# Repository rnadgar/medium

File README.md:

# OpenRegister — Zigbee Smart HVAC Register

A battery-powered, drop-in smart floor register for **room-by-room temperature
control** with Home Assistant. Replaces a standard 4"×10" floor register with a
3D-printed unit containing a stepper-driven damper, limit switches, a
differential-pressure fail-safe, and a Zigbee radio that runs 1–2+ years on
4× AA lithium cells.

```
Wall temp sensor ──► Home Assistant ──► Zigbee ──► register damper position
                          ▲                              │
                          └──── pressure / battery ◄─────┘
```

| PCB rev A (front) | Mechanism (faceplate hidden) |
|---|---|
|  |  |

## Highlights

- **Zigbee sleepy end device** (ESP32-C6) — pairs with Zigbee2MQTT or ZHA and
  appears in Home Assistant as a `cover` entity with a position slider.
- **Fine-grained damper control** — 28BYJ-48 geared stepper (bipolar-modified,
  DRV8833 driver) with limit switches for homing; motor fully de-energized
  between moves.
- **Autonomous pressure fail-safe** — an onboard differential pressure sensor
  trips the damper fully open if duct static pressure exceeds a threshold,
  with **no network dependency**; an HA-side blueprint additionally keeps the
  total open area across all registers above a configurable floor.
- **Ultra-low power** — ~150 µA average draw ⇒ ≈2.4 years on 4× AA lithium
  (see [docs/power-budget.md](docs/power-budget.md)).
- **Fully parametric CAD** — the whole register is generated from one
  parameters dataclass ([build123d](https://build123d.readthedocs.io/)), so
  other register sizes are a preset away.

## Repository layout

| Path | Contents |
|---|---|
| [`docs/`](docs/) | Architecture, power budget, BOM, assembly, pairing guides |
| [`firmware/`](firmware/) | ESP-IDF + esp-zigbee-sdk firmware (C) with host-runnable unit tests |
| [`hardware/pcb/`](hardware/pcb/) | KiCad schematic + layout, fab outputs |
| [`cad/`](cad/) | build123d parametric models, STL/STEP export, pytest checks |
| [`homeassistant/`](homeassistant/) | Zigbee2MQTT converter, ZHA quirk, HA blueprints |

## Getting started

1. **Read** [docs/architecture.md](docs/architecture.md) for the system design.
2. **Buy** the parts in [docs/bom.md](docs/bom.md).
3. **Print** the register: `cd cad && pip install -e . && python export.py`
   then print the STLs in `cad/out/stl/` ([docs/assembly.md](docs/assembly.md)).
4. **Flash** the firmware: `cd firmware && idf.py set-target esp32c6 && idf.py flash`.
5. **Pair** with Zigbee2MQTT and import the blueprints
   ([docs/pairing-setup.md](docs/pairing-setup.md)).

## Status

Rev A — design complete, hardware validation in progress. Firmware bring-up
happens on an ESP32-C6-DevKitC-1 with breakout boards **before** ordering the
custom PCB; see the dev-bench section of the BOM.

## License

MIT — see [LICENSE](LICENSE).

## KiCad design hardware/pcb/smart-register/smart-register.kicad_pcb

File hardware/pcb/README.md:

# smart-register rev A — PCB

58 × 38 mm 2-layer board for the e-bay of the smart register. ESP32-C6-MINI-1
(Zigbee), TPS62125 always-on 3.3 V buck, DRV8833 stepper driver on a
TPS22810-switched battery rail, SiP32431-switched 3.3 V sensor rail,
XGZP6897D on-board differential pressure sensor (or SDP810 on the J5 remote
header), gated battery divider, limit-switch inputs, USB-C flash/debug.

## Layout facts

- Outline/mounting contract with `cad/smart_register/params.py`:
  58 × 38 mm, M3 holes inset 3.5 mm from each corner.
- ESP32-C6 antenna at the **left board edge** with a copper/track keep-out
  under it; the CAD e-bay mounts the board vertically so this edge sits in
  the top 15 mm of the register (above the steel boot line).
- Net classes: `Default` 0.3 mm / 0.2 mm clearance; `USB` (fine-pitch USB-C
  and WSON buck nets) 0.2 mm / 0.13 mm.
- DRC: clean under KiCad 8 with the project file's net classes and severity
  settings (silk cosmetics and lib checks off — all footprints are embedded).

## Regenerating everything

The whole board is **generated from code** — do not hand-edit the outputs;
edit `tools/design.py` (netlist), `tools/gen_pcb.py` (placement), or the
generators, then:

```bash
cd hardware/pcb/tools
python3 design.py            # validate the canonical netlist
python3 gen_project.py       # .kicad_pro + lib tables
python3 gen_schematic.py     # smart-register.kicad_sch
python3 check_netlist.py     # schematic netlist == design.py (kicad-cli)
python3 gen_pcb.py           # placed board + Specctra DSN
java -jar freerouting.jar -de ../smart-register/smart-register.dsn \
     -do ../smart-register/smart-register.ses -mp 30
python3 import_ses.py        # tracks/vias + repairs + pours + stitching + DRC
python3 gen_fab.py           # gerbers/drill/BOM/CPL into ../fab/
```

Requires KiCad 7+ (pcbnew python + kicad-cli) and Java 17+ for
[Freerouting](https://github.com/freerouting/freerouting). The committed
`smart-register.ses` reproduces the committed routing exactly; only re-run
Freerouting if you change the design, and re-check DRC afterwards
(`import_ses.py` prints "DRC real issues: none" on success — its hand-repair
coordinates in `REPAIRS` are tied to the committed session and must be
revisited after any re-route).

## Ordering (JLCPCB)

1. Upload `fab/smart-register-gerbers.zip` — 2-layer, 1.6 mm FR4, any color,
   HASL or ENIG, no special options.
2. Optional assembly: `fab/bom.csv` + `fab/cpl.csv` (verify rotations in
   their preview — generated rotations follow KiCad, JLC sometimes differs
   per package).
3. **Order after validating firmware on the dev bench** (see
   `docs/bom.md` section E) — the board is validation, not the critical path.

## Bring-up checklist

1. Visual + shorts check (VBAT–GND, 3V3–GND).
2. Batteries in (or USB — SS14 feeds the pack rail at ~4.7 V for bench work):
   3.3 V rail present, ~40 µA sleep draw after flashing.
3. Flash via USB-C (`idf.py -p /dev/ttyACM0 flash` — USB-Serial-JTAG).
4. `MOTOR_PWR_EN` high → VMOT = pack voltage, sensor rail 3.3 V.
5. Motor moves, limit switches read, pressure sample returns plausible Pa.
6. Join Zigbee, then the `docs/pairing-setup.md` flow.

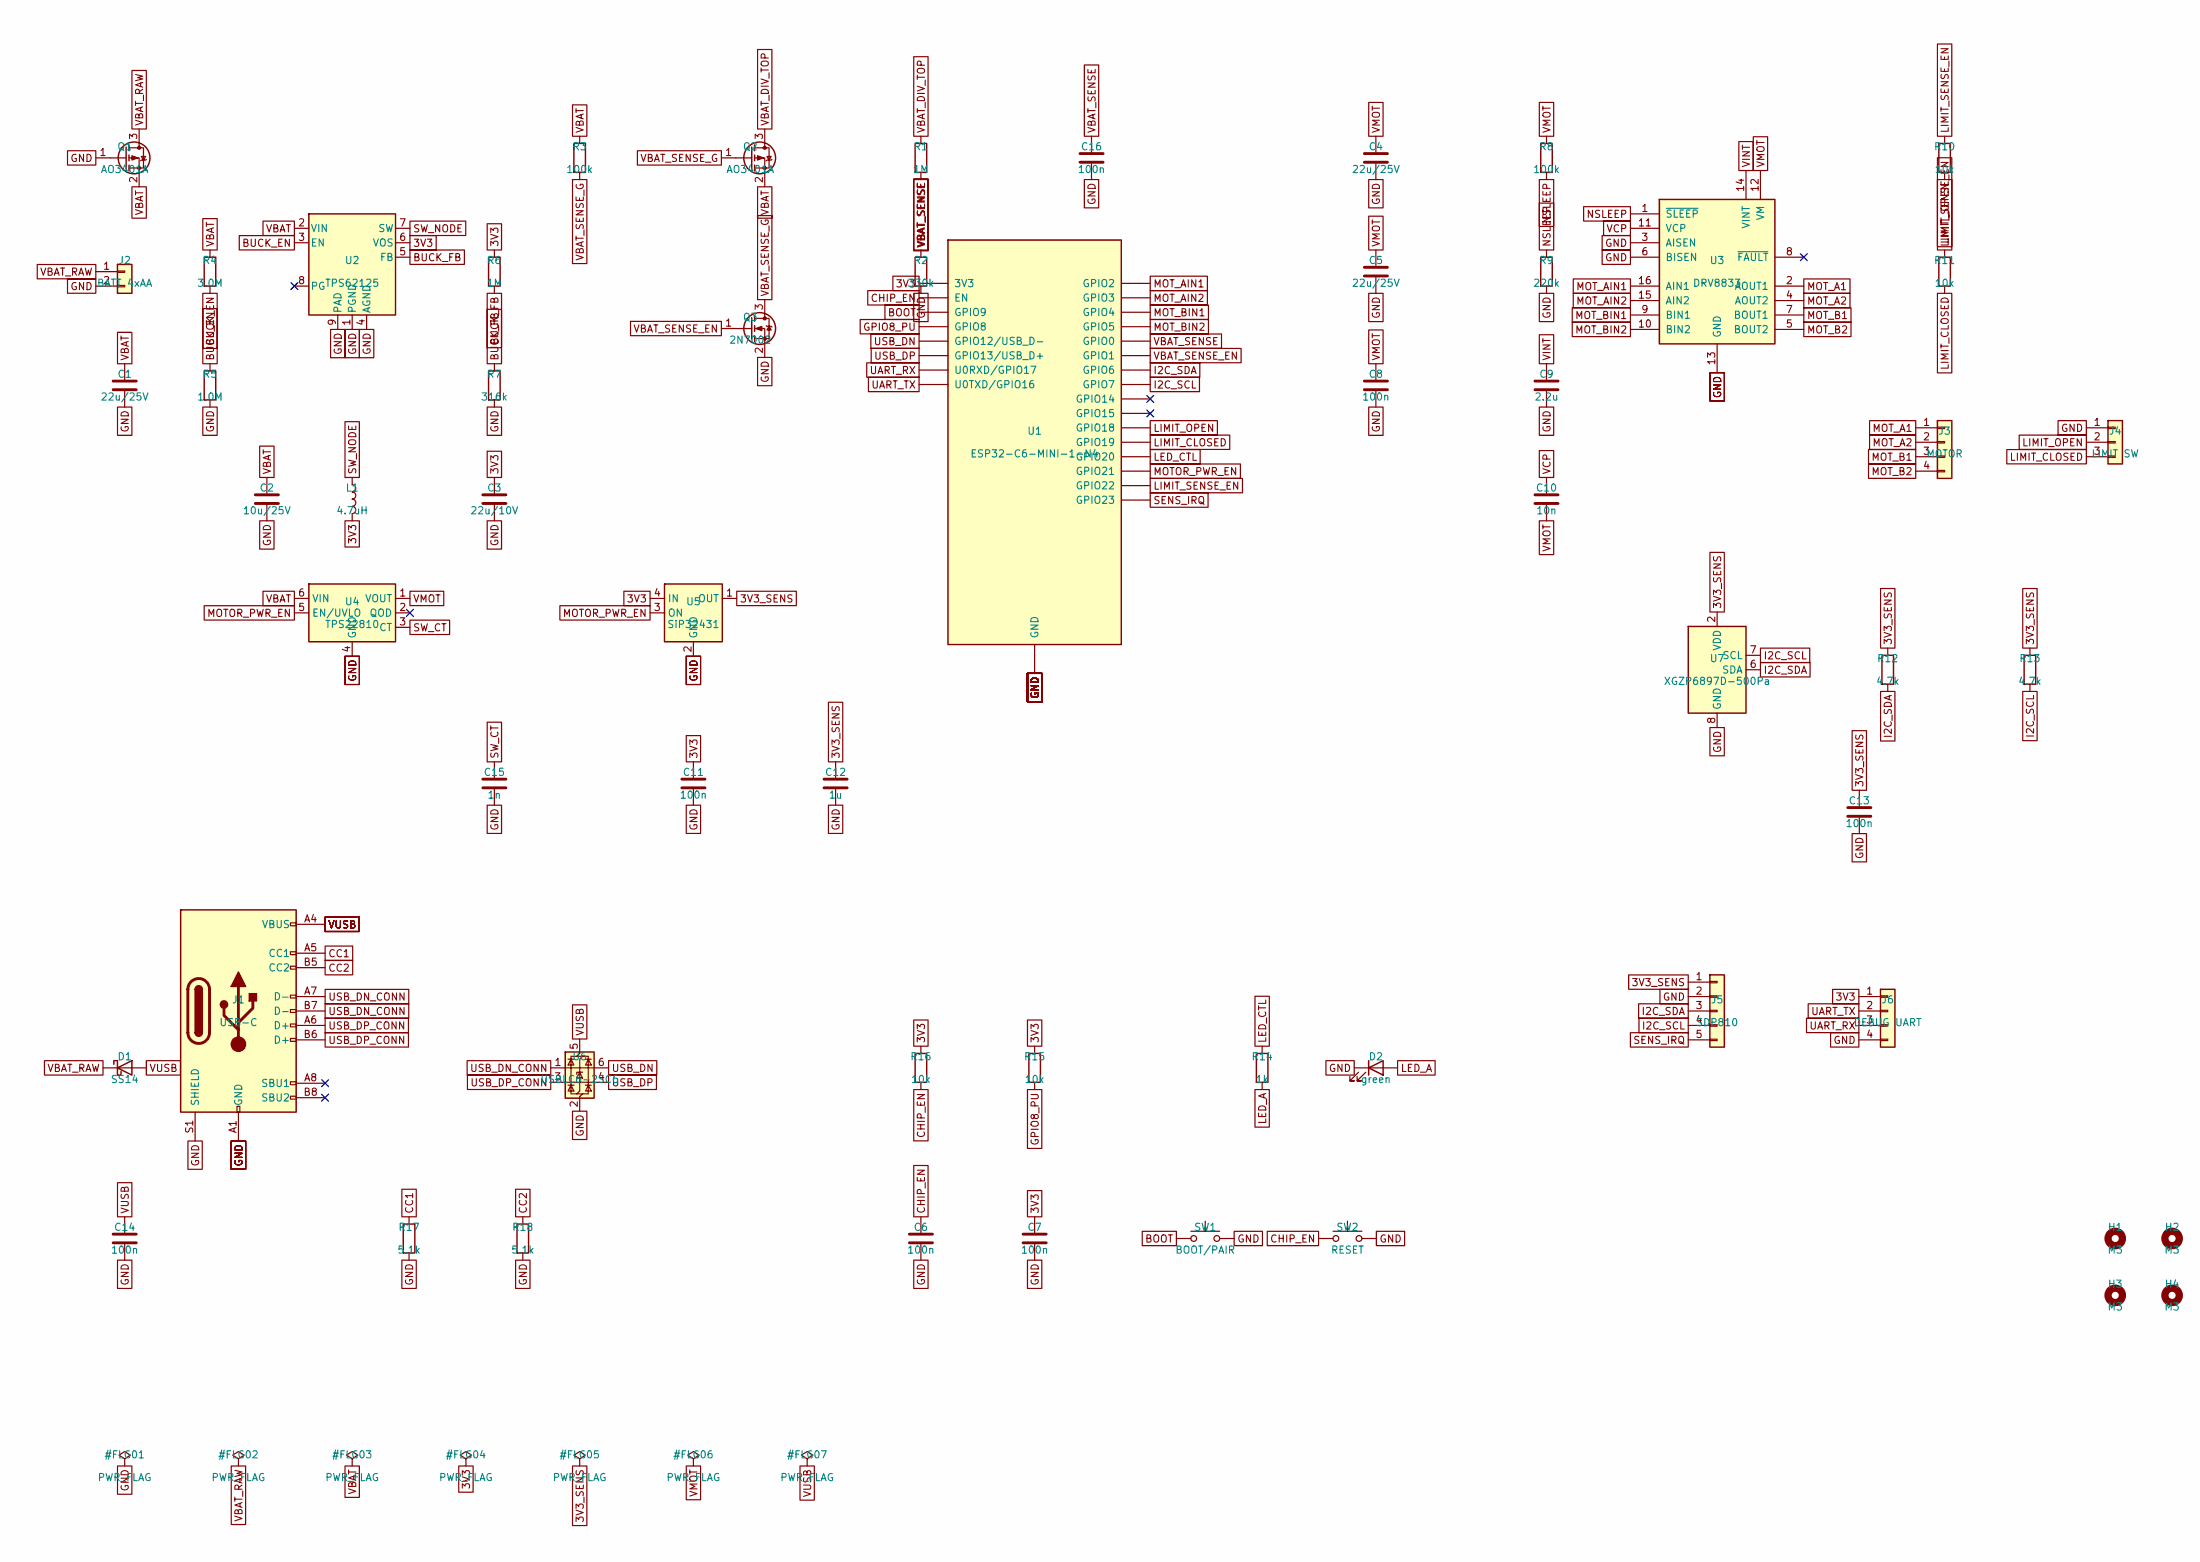
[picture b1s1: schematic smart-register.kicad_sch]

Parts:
C1, C4, C5: 22u/25V; C_1206_3216Metric; MPN GRM31CR61E226KE15
C2: 10u/25V; C_0805_2012Metric; MPN GRM21BR61E106KA73
C3: 22u/10V; C_0805_2012Metric; MPN GRM21BR61A226ME44
C6, C7, C8, C11, C13, C14, C16: 100n; C_0603_1608Metric; MPN CL10B104KB8NNNC
C9: 2.2u; C_0603_1608Metric; MPN CL10A225KP8NNNC
C10: 10n; C_0603_1608Metric; MPN CL10B103KB8NNNC
C12: 1u; C_0603_1608Metric; MPN CL10A105KB8NNNC
C15: 1n; C_0603_1608Metric; MPN CL10B102KB8NNNC
D1: SS14; D_SMA; MPN SS14
D2: green; LED_0603_1608Metric; MPN 150060GS75000
H1, H2, H3, H4: M3; MountingHole_3.2mm_M3
J1: USB-C; USB_C_Receptacle_GCT_USB4105-xx-A_16P_TopMnt_Horizontal; MPN GCT USB4105-GF-A
J2: BATT 4xAA; JST_PH_S2B-PH-K_1x02_P2.00mm_Horizontal; MPN JST S2B-PH-K-S
J3: MOTOR; JST_PH_B4B-PH-K_1x04_P2.00mm_Vertical; MPN JST B4B-PH-K-S
J4: LIMIT SW; JST_PH_B3B-PH-K_1x03_P2.00mm_Vertical; MPN JST B3B-PH-K-S
J5: SDP810; PinHeader_1x05_P2.54mm_Vertical; MPN header 1x5
J6: DEBUG UART; PinHeader_1x04_P2.54mm_Vertical; MPN header 1x4
L1: 4.7uH; L_Coilcraft_LPS4018; MPN LPS4018-472MRB
Q1, Q2: AO3401A; SOT-23; MPN AO3401A
Q3: 2N7002; SOT-23; MPN 2N7002-7-F
R1, R6: 1M; R_0603_1608Metric; MPN RC0603FR-071ML
R2: 330k; R_0603_1608Metric; MPN RC0603FR-07330KL
R3, R8: 100k; R_0603_1608Metric; MPN RC0603FR-07100KL
R4: 3.0M; R_0603_1608Metric; MPN RC0603FR-073ML
R5: 1.0M; R_0603_1608Metric; MPN RC0603FR-071ML
R7: 316k; R_0603_1608Metric; MPN RC0603FR-07316KL
R9: 220k; R_0603_1608Metric; MPN RC0603FR-07220KL
R10, R11, R15, R16: 10k; R_0603_1608Metric; MPN RC0603FR-0710KL
R12, R13: 4.7k; R_0603_1608Metric; MPN RC0603FR-074K7L
R14: 1k; R_0603_1608Metric; MPN RC0603FR-071KL
R17, R18: 5.1k; R_0603_1608Metric; MPN RC0603FR-075K1L
SW1: BOOT/PAIR; SW_Push_1P1T_NO_CK_KMR2; MPN KMR221GLFS
SW2: RESET; SW_Push_1P1T_NO_CK_KMR2; MPN KMR221GLFS
U1: ESP32-C6-MINI-1-N4; ESP32-C6-MINI-1; MPN ESP32-C6-MINI-1-N4
U2: TPS62125; WSON-8-1EP_2x2mm_P0.5mm_EP0.9x1.6mm; MPN TPS62125DSGR
U3: DRV8833; HTSSOP-16-1EP_4.4x5mm_P0.65mm_EP3.4x5mm; MPN DRV8833PWPR
U4: TPS22810; WSON-6-1EP_2x2mm_P0.65mm_EP1x1.6mm; MPN TPS22810DRVR
U5: SiP32431; SOT-363_SC-70-6; MPN SIP32431DR3-T1GE3
U6: USBLC6-2SC6; SOT-23-6; MPN USBLC6-2SC6
U7: XGZP6897D-500Pa; CFSensor_XGZP6897x; MPN XGZP6897D (+-500Pa I2C)

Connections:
3V3: C3.1, C7.1, C11.1, J6.1, L1.2, R6.1, R15.1, R16.1, U1.3 (3V3), U2.6 (VOS), U5.4 (IN)
3V3_SENS: C12.1, C13.1, J5.1, R12.1, R13.1, U5.1 (OUT), U7.2 (VDD)
BOOT: SW1.1, U1.23 (GPIO9)
BUCK_EN: R4.2, R5.1, U2.3 (EN)
BUCK_FB: R6.2, R7.1, U2.5 (FB)
CC1: J1.A5 (CC1), R17.1
CC2: J1.B5 (CC2), R18.1
CHIP_EN: C6.1, R16.2, SW2.1, U1.8 (EN)
GND: C1.2, C2.2, C3.2, C4.2, C5.2, C6.2, C7.2, C8.2, C9.2, C11.2, C12.2, C13.2, C14.2, C15.2, C16.2, D2.1 (K), J1.A1 (GND), J1.A12 (GND), J1.B1 (GND), J1.B12 (GND), J1.S1 (SHIELD), J2.2, J4.1, J5.2, J6.4, Q1.1 (G), Q3.2 (S), R2.2, R5.2, R7.2, R9.2, R17.2, R18.2, SW1.2, SW2.2, U1.1 (GND), U1.2 (GND), U1.11 (GND), U1.14 (GND), U1.34 (NC), U1.36 (GND), U1.37 (GND), U1.38 (GND), U1.39 (GND), U1.40 (GND), U1.41 (GND), U1.42 (GND), U1.43 (GND), U1.44 (GND), U1.45 (GND), U1.46 (GND), U1.47 (GND), U1.48 (GND), U1.49 (GND), U1.50 (GND), U1.51 (GND), U1.52 (GND), U1.53 (GND), U2.1 (PGND), U2.4 (AGND), U2.9 (PAD), U3.3 (AISEN), U3.6 (BISEN), U3.13 (GND), U3.17 (GND), U4.4 (GND), U4.7 (GND), U5.2 (GND), U5.5 (GND), U6.2 (GND), U7.8 (GND)
GPIO8_PU: R15.2, U1.22 (GPIO8)
I2C_SCL: J5.4, R13.2, U1.16 (GPIO7), U7.7 (SCL)
I2C_SDA: J5.3, R12.2, U1.15 (GPIO6), U7.6 (SDA)
LED_A: D2.2 (A), R14.2
LED_CTL: R14.1, U1.26 (GPIO20)
LIMIT_CLOSED: J4.3, R11.2, U1.25 (GPIO19)
LIMIT_OPEN: J4.2, R10.2, U1.24 (GPIO18)
LIMIT_SENSE_EN: R10.1, R11.1, U1.28 (GPIO22)
MOTOR_PWR_EN: U1.27 (GPIO21), U4.5 (EN/UVLO), U5.3 (ON)
MOT_A1: J3.1, U3.2 (AOUT1)
MOT_A2: J3.2, U3.4 (AOUT2)
MOT_AIN1: U1.5 (GPIO2), U3.16 (AIN1)
MOT_AIN2: U1.6 (GPIO3), U3.15 (AIN2)
MOT_B1: J3.3, U3.7 (BOUT1)
MOT_B2: J3.4, U3.5 (BOUT2)
MOT_BIN1: U1.9 (GPIO4), U3.9 (BIN1)
MOT_BIN2: U1.10 (GPIO5), U3.10 (BIN2)
NSLEEP: R8.2, R9.1, U3.1 (~SLEEP)
SENS_IRQ: J5.5, U1.29 (GPIO23)
SW_CT: C15.1, U4.3 (CT)
SW_NODE: L1.1, U2.7 (SW)
UART_RX: J6.3, U1.30 (U0RXD/GPIO17)
UART_TX: J6.2, U1.31 (U0TXD/GPIO16)
USB_DN: U1.17 (GPIO12/USB_D-), U6.6 (I/O1)
USB_DN_CONN: J1.A7 (D-), J1.B7 (D-), U6.1 (I/O1)
USB_DP: U1.18 (GPIO13/USB_D+), U6.4 (I/O2)
USB_DP_CONN: J1.A6 (D+), J1.B6 (D+), U6.3 (I/O2)
VBAT: C1.1, C2.1, Q1.2 (S), Q2.2 (S), R3.1, R4.1, U2.2 (VIN), U4.6 (VIN)
VBAT_DIV_TOP: Q2.3 (D), R1.1
VBAT_RAW: D1.1 (K), J2.1, Q1.3 (D)
VBAT_SENSE: C16.1, R1.2, R2.1, U1.12 (GPIO0)
VBAT_SENSE_EN: Q3.1 (G), U1.13 (GPIO1)
VBAT_SENSE_G: Q2.1 (G), Q3.3 (D), R3.2
VCP: C10.1, U3.11 (VCP)
VINT: C9.1, U3.14 (VINT)
VMOT: C4.1, C5.1, C8.1, C10.2, R8.1, U3.12 (VM), U4.1 (VOUT)
VUSB: C14.1, D1.2 (A), J1.A4 (VBUS), J1.A9 (VBUS), J1.B4 (VBUS), J1.B9 (VBUS), U6.5 (VBUS)

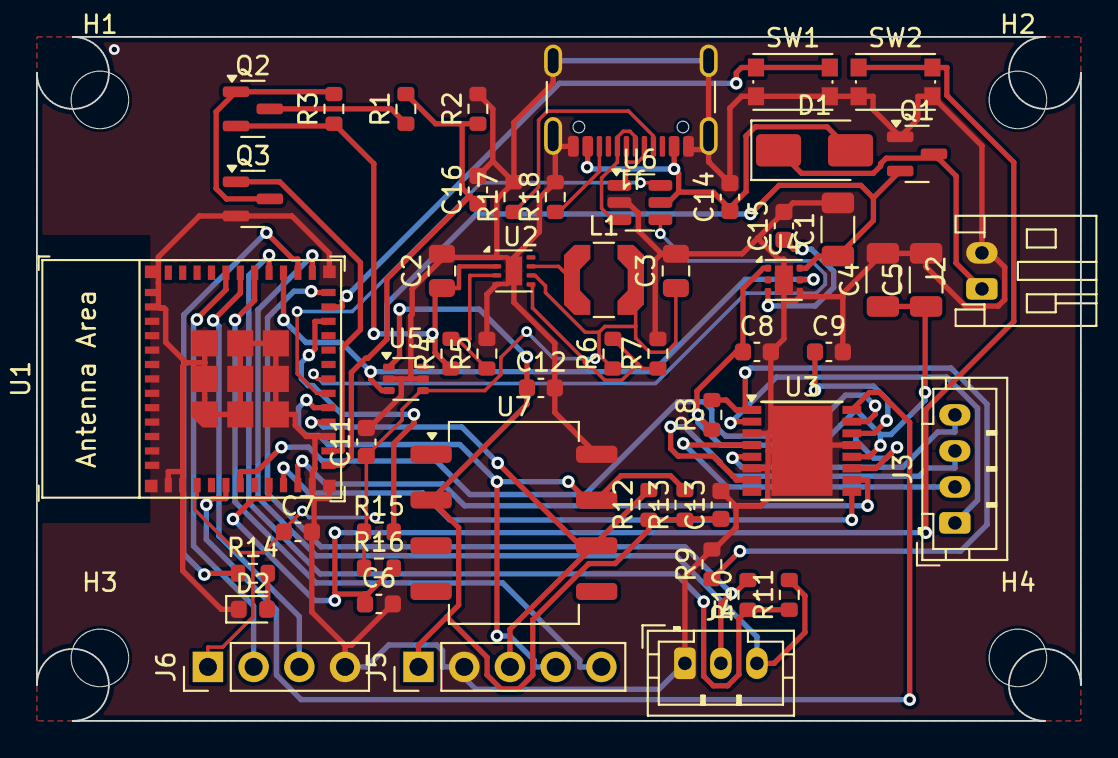
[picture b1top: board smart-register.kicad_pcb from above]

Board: 2 copper layers, 58.0 x 38.0 mm, 59 parts (1 on the bottom side), 46 nets.

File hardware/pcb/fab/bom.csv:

Comment,Designator,Footprint,MPN,Qty
22u/25V,"C1,C4,C5",C_1206_3216Metric,GRM31CR61E226KE15,3
10n,C10,C_0603_1608Metric,CL10B103KB8NNNC,1
1u,C12,C_0603_1608Metric,CL10A105KB8NNNC,1
1n,C15,C_0603_1608Metric,CL10B102KB8NNNC,1
10u/25V,C2,C_0805_2012Metric,GRM21BR61E106KA73,1
22u/10V,C3,C_0805_2012Metric,GRM21BR61A226ME44,1
100n,"C11,C13,C14,C16,C6,C7,C8",C_0603_1608Metric,CL10B104KB8NNNC,7
2.2u,C9,C_0603_1608Metric,CL10A225KP8NNNC,1
SS14,D1,D_SMA,SS14,1
green,D2,LED_0603_1608Metric,150060GS75000,1
USB-C,J1,USB_C_Receptacle_GCT_USB4105-xx-A_16P_TopMnt_Horizontal,GCT USB4105-GF-A,1
BATT 4xAA,J2,JST_PH_S2B-PH-K_1x02_P2.00mm_Horizontal,JST S2B-PH-K-S,1
MOTOR,J3,JST_PH_B4B-PH-K_1x04_P2.00mm_Vertical,JST B4B-PH-K-S,1
LIMIT SW,J4,JST_PH_B3B-PH-K_1x03_P2.00mm_Vertical,JST B3B-PH-K-S,1
SDP810,J5,PinHeader_1x05_P2.54mm_Vertical,header 1x5,1
DEBUG UART,J6,PinHeader_1x04_P2.54mm_Vertical,header 1x4,1
4.7uH,L1,L_Coilcraft_LPS4018,LPS4018-472MRB,1
AO3401A,"Q1,Q2",SOT-23,AO3401A,2
2N7002,Q3,SOT-23,2N7002-7-F,1
1M,"R1,R6",R_0603_1608Metric,RC0603FR-071ML,2
10k,"R10,R11,R15,R16",R_0603_1608Metric,RC0603FR-0710KL,4
4.7k,"R12,R13",R_0603_1608Metric,RC0603FR-074K7L,2
1k,R14,R_0603_1608Metric,RC0603FR-071KL,1
5.1k,"R17,R18",R_0603_1608Metric,RC0603FR-075K1L,2
330k,R2,R_0603_1608Metric,RC0603FR-07330KL,1
100k,"R3,R8",R_0603_1608Metric,RC0603FR-07100KL,2
3.0M,R4,R_0603_1608Metric,RC0603FR-073ML,1
1.0M,R5,R_0603_1608Metric,RC0603FR-071ML,1
316k,R7,R_0603_1608Metric,RC0603FR-07316KL,1
220k,R9,R_0603_1608Metric,RC0603FR-07220KL,1
BOOT/PAIR,SW1,SW_Push_1P1T_NO_CK_KMR2,KMR221GLFS,1
RESET,SW2,SW_Push_1P1T_NO_CK_KMR2,KMR221GLFS,1
ESP32-C6-MINI-1-N4,U1,ESP32-C6-MINI-1,ESP32-C6-MINI-1-N4,1
TPS62125,U2,WSON-8-1EP_2x2mm_P0.5mm_EP0.9x1.6mm,TPS62125DSGR,1
DRV8833,U3,HTSSOP-16-1EP_4.4x5mm_P0.65mm_EP3.4x5mm,DRV8833PWPR,1
TPS22810,U4,WSON-6-1EP_2x2mm_P0.65mm_EP1x1.6mm,TPS22810DRVR,1
SiP32431,U5,SOT-363_SC-70-6,SIP32431DR3-T1GE3,1
USBLC6-2SC6,U6,SOT-23-6,USBLC6-2SC6,1
XGZP6897D-500Pa,U7,CFSensor_XGZP6897x,XGZP6897D (+-500Pa I2C),1

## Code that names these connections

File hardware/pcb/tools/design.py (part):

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        mpn="ESP32-C6-MINI-1-N4", desc="Zigbee module, PCB antenna",
        pins={
            "1": GND, "2": GND, "3": "3V3", "4": NC,
            "5": "MOT_AIN1",        # GPIO2
            "6": "MOT_AIN2",        # GPIO3
            "7": NC,
            "8": "CHIP_EN",         # EN/CHIP_PU
            "9": "MOT_BIN1",        # GPIO4
            "10": "MOT_BIN2",       # GPIO5
            "11": GND,
            "12": "VBAT_SENSE",     # GPIO0 / ADC1_CH0
            "13": "VBAT_SENSE_EN",  # GPIO1
            "14": GND,
            "15": "I2C_SDA",        # GPIO6
            "16": "I2C_SCL",        # GPIO7
            "17": "USB_DN",         # GPIO12 / USB_D-
            "18": "USB_DP",         # GPIO13 / USB_D+
            "19": NC,               # GPIO14 spare
            "20": NC,               # GPIO15 spare
            "21": NC,
            "22": "GPIO8_PU",       # GPIO8 boot strap
            "23": "BOOT",           # GPIO9 boot / pairing button
            "24": "LIMIT_OPEN",     # GPIO18
            "25": "LIMIT_CLOSED",   # GPIO19
            "26": "LED_CTL",        # GPIO20
            "27": "MOTOR_PWR_EN",   # GPIO21
            "28": "LIMIT_SENSE_EN", # GPIO22
            "29": "SENS_IRQ",       # GPIO23 spare on sensor header
            "30": "UART_RX",        # U0RXD / GPIO17
            "31": "UART_TX",        # U0TXD / GPIO16
            **{str(n): NC for n in (32, 33, 34, 35)},
            **{str(n): GND for n in range(36, 54)},
        },
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        lib="Regulator_Switching", sym="TPS62125DSG", value="TPS62125",
        footprint="Package_SON:WSON-8-1EP_2x2mm_P0.5mm_EP0.9x1.6mm",
        mpn="TPS62125DSGR", desc="Buck 3.3 V always-on, Iq 13 uA",
        pins={"1": GND, "2": "VBAT", "3": "BUCK_EN", "4": GND,
              "5": "BUCK_FB", "6": "3V3", "7": "SW_NODE", "8": NC, "9": GND},
        sch=(80, 60),
    ),
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        lib="Driver_Motor", sym="DRV8833PWP", value="DRV8833",
        footprint="Package_SO:HTSSOP-16-1EP_4.4x5mm_P0.65mm_EP3.4x5mm",
        mpn="DRV8833PWPR", desc="Stepper driver (bipolar-modded 28BYJ-48)",
        pins={"1": "NSLEEP", "2": "MOT_A1", "3": GND, "4": "MOT_A2",
              "5": "MOT_B2", "6": GND, "7": "MOT_B1", "8": NC,
              "9": "MOT_BIN1", "10": "MOT_BIN2", "11": "VCP", "12": "VMOT",
              "13": GND, "14": "VINT", "15": "MOT_AIN2", "16": "MOT_AIN1",
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        lib="Power_Management", sym="TPS22810DRV", value="TPS22810",
        footprint="Package_SON:WSON-6-1EP_2x2mm_P0.65mm_EP1x1.6mm",
        mpn="TPS22810DRVR", desc="Motor rail load switch, 18 V rated",
        pins={"1": "VMOT", "2": NC, "3": "SW_CT", "4": GND,
              "5": "MOTOR_PWR_EN", "6": "VBAT", "7": GND},
        sch=(80, 120),
    ),
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        lib="Power_Management", sym="SiP32431DR3", value="SiP32431",
        footprint="Package_TO_SOT_SMD:SOT-363_SC-70-6",
        mpn="SIP32431DR3-T1GE3", desc="Sensor 3.3 V load switch, 10 nA leak",
        pins={"1": "3V3_SENS", "2": GND, "3": "MOTOR_PWR_EN", "4": "3V3",
              "5": GND, "6": NC},
        sch=(140, 120),
    ),
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        lib="Power_Protection", sym="USBLC6-2SC6", value="USBLC6-2SC6",
        footprint="Package_TO_SOT_SMD:SOT-23-6",
        mpn="USBLC6-2SC6", desc="USB ESD protection",
        pins={"1": "USB_DN_CONN", "2": GND, "3": "USB_DP_CONN",
              "4": "USB_DP", "5": "VUSB", "6": "USB_DN"},
        sch=(120, 200),
    ),
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        lib="Transistor_FET", sym="AO3401A", value="AO3401A",
        footprint="Package_TO_SOT_SMD:SOT-23",
        mpn="AO3401A", desc="Reverse-polarity protection P-FET",
        pins={"1": GND, "2": "VBAT", "3": "VBAT_RAW"},
        sch=(40, 40),
    ),
    "Q2": dict(
        lib="Transistor_FET", sym="AO3401A", value="AO3401A",
        footprint="Package_TO_SOT_SMD:SOT-23",
        mpn="AO3401A", desc="Battery divider high-side switch",
        pins={"1": "VBAT_SENSE_G", "2": "VBAT", "3": "VBAT_DIV_TOP"},
        sch=(150, 40),
    ),
    "Q3": dict(
        lib="Transistor_FET", sym="2N7002", value="2N7002",
        footprint="Package_TO_SOT_SMD:SOT-23",
        mpn="2N7002-7-F", desc="Divider gate driver",
        pins={"1": "VBAT_SENSE_EN", "2": GND, "3": "VBAT_SENSE_G"},
        sch=(150, 70),
    ),
    "D1": dict(
        lib="Device", sym="D_Schottky", value="SS14",
        footprint="Diode_SMD:D_SMA",
        mpn="SS14", desc="USB bench power injection (into VBAT_RAW, pre-FET)",
        pins={"1": "VBAT_RAW", "2": "VUSB"},  # 1=K 2=A
        sch=(40, 200),
    ),
    "D2": dict(
        lib="Device", sym="LED", value="green",
        footprint="LED_SMD:LED_0603_1608Metric",
        mpn="150060GS75000", desc="Status LED",
        pins={"1": GND, "2": "LED_A"},  # 1=K 2=A
        sch=(260, 200),
    ),
    # --- resistors ---
    "R1": dict(lib="Device", sym="R", value="1M", footprint="Resistor_SMD:R_0603_1608Metric",
               mpn="RC0603FR-071ML", desc="VBAT divider top",
               pins={"1": "VBAT_DIV_TOP", "2": "VBAT_SENSE"}, sch=(180, 40)),
    "R2": dict(lib="Device", sym="R", value="330k", footprint="Resistor_SMD:R_0603_1608Metric",
               mpn="RC0603FR-07330KL", desc="VBAT divider bottom",
               pins={"1": "VBAT_SENSE", "2": GND}, sch=(180, 60)),
    "R3": dict(lib="Device", sym="R", value="100k", footprint="Resistor_SMD:R_0603_1608Metric",
               mpn="RC0603FR-07100KL", desc="Q2 gate pull-up",
               pins={"1": "VBAT", "2": "VBAT_SENSE_G"}, sch=(120, 40)),
    "R4": dict(lib="Device", sym="R", value="3.0M", footprint="Resistor_SMD:R_0603_1608Metric",
               mpn="RC0603FR-073ML", desc="Buck EN UVLO top (cutoff ~4.2 V pack)",
               pins={"1": "VBAT", "2": "BUCK_EN"}, sch=(55, 60)),
    "R5": dict(lib="Device", sym="R", value="1.0M", footprint="Resistor_SMD:R_0603_1608Metric",
               mpn="RC0603FR-071ML", desc="Buck EN UVLO bottom",
               pins={"1": "BUCK_EN", "2": GND}, sch=(55, 80)),
    "R6": dict(lib="Device", sym="R", value="1M", footprint="Resistor_SMD:R_0603_1608Metric",
               mpn="RC0603FR-071ML", desc="Buck FB top",
               pins={"1": "3V3", "2": "BUCK_FB"}, sch=(105, 60)),
    "R7": dict(lib="Device", sym="R", value="316k", footprint="Resistor_SMD:R_0603_1608Metric",
               mpn="RC0603FR-07316KL", desc="Buck FB bottom (Vout 3.33 V)",
               pins={"1": "BUCK_FB", "2": GND}, sch=(105, 80)),
    "R8": dict(lib="Device", sym="R", value="100k", footprint="Resistor_SMD:R_0603_1608Metric",
               mpn="RC0603FR-07100KL", desc="DRV8833 nSLEEP divider top (from VMOT)",
               pins={"1": "VMOT", "2": "NSLEEP"}, sch=(290, 40)),
    "R9": dict(lib="Device", sym="R", value="220k", footprint="Resistor_SMD:R_0603_1608Metric",
               mpn="RC0603FR-07220KL", desc="nSLEEP divider bottom",
               pins={"1": "NSLEEP", "2": GND}, sch=(290, 60)),
    "R10": dict(lib="Device", sym="R", value="10k", footprint="Resistor_SMD:R_0603_1608Metric",
                mpn="RC0603FR-0710KL", desc="Limit OPEN pull-up (gated)",
                pins={"1": "LIMIT_SENSE_EN", "2": "LIMIT_OPEN"}, sch=(360, 40)),
    "R11": dict(lib="Device", sym="R", value="10k", footprint="Resistor_SMD:R_0603_1608Metric",
                mpn="RC0603FR-0710KL", desc="Limit CLOSED pull-up (gated)",
                pins={"1": "LIMIT_SENSE_EN", "2": "LIMIT_CLOSED"}, sch=(360, 60)),
    "R12": dict(lib="Device", sym="R", value="4.7k", footprint="Resistor_SMD:R_0603_1608Metric",
                mpn="RC0603FR-074K7L", desc="I2C SDA pull-up (switched rail)",
                pins={"1": "3V3_SENS", "2": "I2C_SDA"}, sch=(350, 130)),
    "R13": dict(lib="Device", sym="R", value="4.7k", footprint="Resistor_SMD:R_0603_1608Metric",
                mpn="RC0603FR-074K7L", desc="I2C SCL pull-up (switched rail)",
                pins={"1": "3V3_SENS", "2": "I2C_SCL"}, sch=(375, 130)),
    "R14": dict(lib="Device", sym="R", value="1k", footprint="Resistor_SMD:R_0603_1608Metric",
                mpn="RC0603FR-071KL", desc="LED series",
                pins={"1": "LED_CTL", "2": "LED_A"}, sch=(240, 200)),
    "R15": dict(lib="Device", sym="R", value="10k", footprint="Resistor_SMD:R_0603_1608Metric",
                mpn="RC0603FR-0710KL", desc="GPIO8 boot strap pull-up",
                pins={"1": "3V3", "2": "GPIO8_PU"}, sch=(200, 200)),
    "R16": dict(lib="Device", sym="R", value="10k", footprint="Resistor_SMD:R_0603_1608Metric",
                mpn="RC0603FR-0710KL", desc="CHIP_EN pull-up",
                pins={"1": "3V3", "2": "CHIP_EN"}, sch=(180, 200)),
    "R17": dict(lib="Device", sym="R", value="5.1k", footprint="Resistor_SMD:R_0603_1608Metric",
                mpn="RC0603FR-075K1L", desc="USB CC1 pull-down (UFP)",
                pins={"1": "CC1", "2": GND}, sch=(90, 230)),
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               pins={"1": "3V3", "2": GND}, sch=(105, 100)),
    "C4": dict(lib="Device", sym="C", value="22u/25V", footprint="Capacitor_SMD:C_1206_3216Metric",
               mpn="GRM31CR61E226KE15", desc="VMOT bulk 1",
               pins={"1": "VMOT", "2": GND}, sch=(260, 40)),
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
